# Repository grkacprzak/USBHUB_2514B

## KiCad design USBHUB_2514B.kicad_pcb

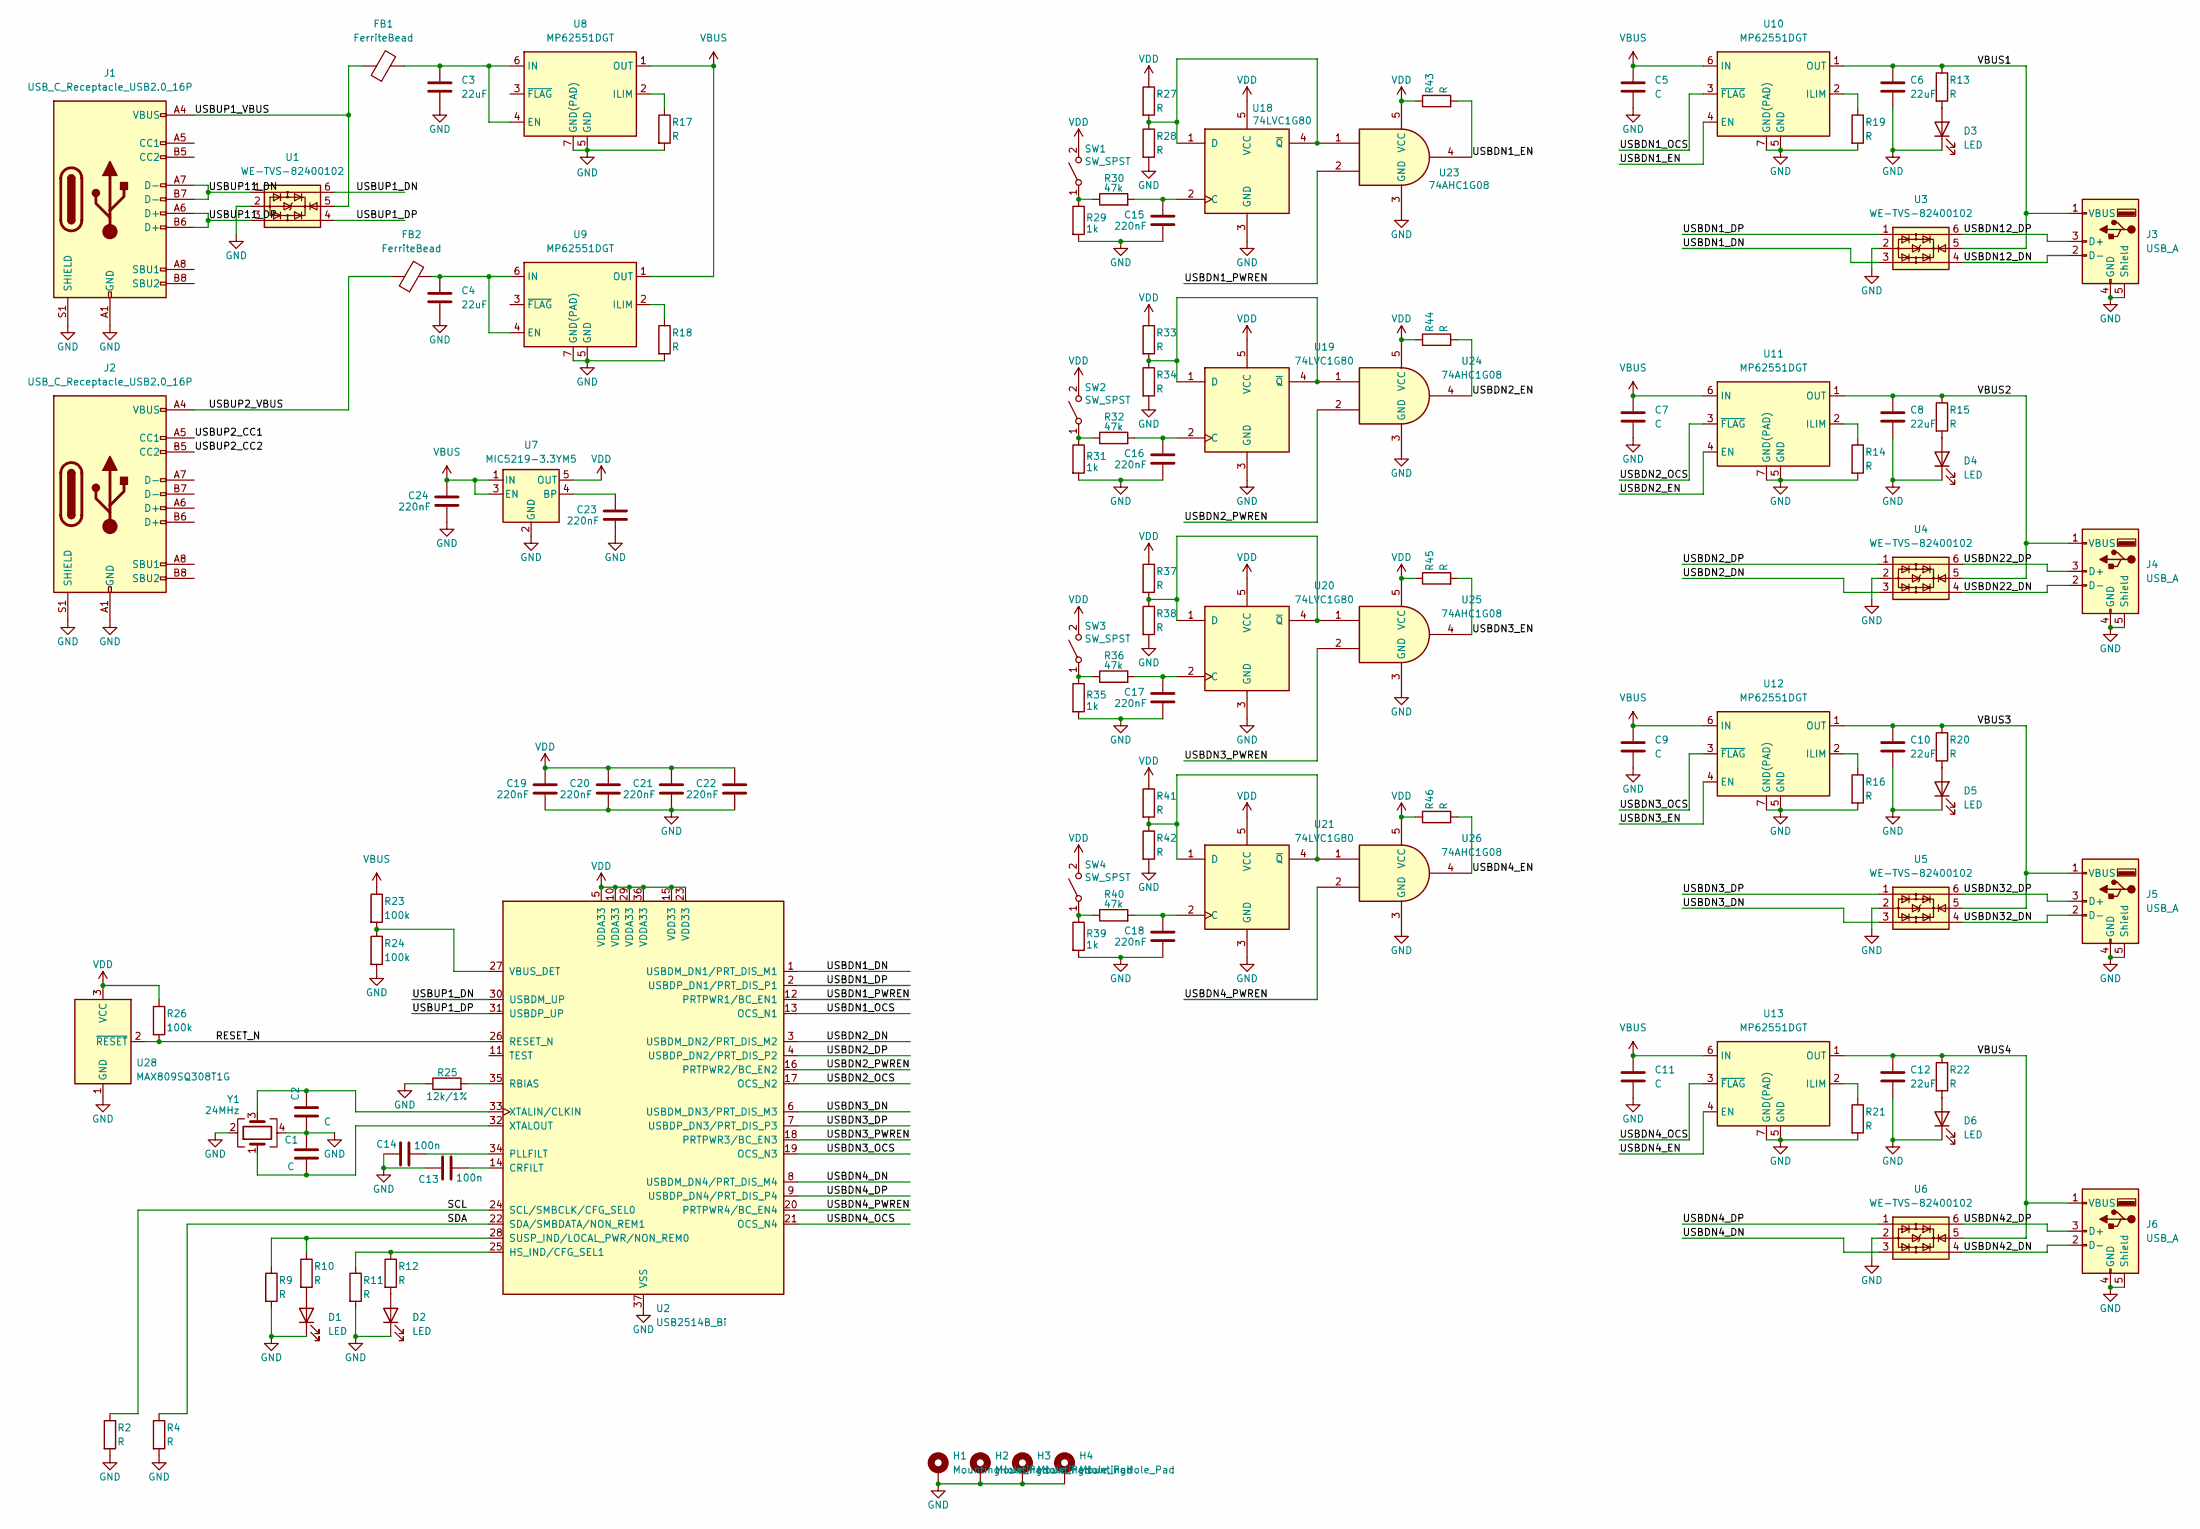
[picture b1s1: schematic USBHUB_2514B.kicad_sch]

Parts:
C1, C2, C5, C7, C9, C11: C; C_0402_1005Metric
C3, C4, C6, C8, C10, C12: 22uF; C_0805_2012Metric
C13, C14: 100n; C_0402_1005Metric
C15, C16, C17, C18, C19, C20, C21, C22, C23, C24: 220nF; C_0402_1005Metric
D1, D2, D3, D4, D5, D6: LED; LED_0603_1608Metric
FB1, FB2: FerriteBead; L_0805_2012Metric
H1, H2, H3, H4: MountingHole_Pad; MountingHole_2.5mm_Pad
J1, J2: USB_C_Receptacle_USB2.0_16P; USB_C_Receptacle_Wuerth_629722000214
J3, J4, J5, J6: USB_A; USB_A_Wuerth_614004185023_Vertical
R2, R4, R9, R10, R11, R12, R13, R14, R15, R16, R17, R18, R19, R20, R21, R22, R27, R28, R33, R34, R37, R38, R41, R42, R43, R44, R45, R46: R; R_0402_1005Metric
R23, R24, R26: 100k; R_0402_1005Metric
R25: 12k/1%; R_0402_1005Metric
R29, R31, R35, R39: 1k; R_0402_1005Metric
R30, R32, R36, R40: 47k; R_0402_1005Metric
SW1, SW2, SW3, SW4: SW_SPST; SW_PUSH_6mm_H9.5mm
U1, U3, U4, U5, U6: WE-TVS-82400102; SOT-363_SC-70-6
U2: USB2514B_Bi; QFN-36-1EP_6x6mm_P0.5mm_EP3.7x3.7mm
U7: MIC5219-3.3YM5; SOT-23-5
U8, U9, U10, U11, U12, U13: MP62551DGT; DFN-6-1EP_2x2mm_P0.65mm_EP1x1.6mm
U18, U19, U20, U21: 74LVC1G80; SOT-353_SC-70-5
U23, U24, U25, U26: 74AHC1G08; SOT-353_SC-70-5
U28: MAX809SQ308T1G; SOT-323_SC-70
Y1: 24MHz; Crystal_SMD_2520-4Pin_2.5x2.0mm

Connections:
/RESET_N: R26.2, U2.26 (RESET_N), U28.2 (~RESET)
/SCL: R2.1, U2.24 (SCL/SMBCLK/CFG_SEL0)
/SDA: R4.1, U2.22 (SDA/SMBDATA/NON_REM1)
/USBDN1_DN: U2.1 (USBDM_DN1/PRT_DIS_M1), U3.3
/USBDN1_DP: U2.2 (USBDP_DN1/PRT_DIS_P1), U3.1
/USBDN1_EN: R43.2, U10.4 (EN), U23.4
/USBDN1_OCS: U2.13 (OCS_N1), U10.3 (~FLAG)
/USBDN1_PWREN: U2.12 (PRTPWR1/BC_EN1), U23.2
/USBDN2_DN: U2.3 (USBDM_DN2/PRT_DIS_M2), U4.3
/USBDN2_DP: U2.4 (USBDP_DN2/PRT_DIS_P2), U4.1
/USBDN2_EN: R44.2, U11.4 (EN), U24.4
/USBDN2_OCS: U2.17 (OCS_N2), U11.3 (~FLAG)
/USBDN2_PWREN: U2.16 (PRTPWR2/BC_EN2), U24.2
/USBDN3_DN: U2.6 (USBDM_DN3/PRT_DIS_M3), U5.3
/USBDN3_DP: U2.7 (USBDP_DN3/PRT_DIS_P3), U5.1
/USBDN3_EN: R45.2, U12.4 (EN), U25.4
/USBDN3_OCS: U2.19 (OCS_N3), U12.3 (~FLAG)
/USBDN3_PWREN: U2.18 (PRTPWR3/BC_EN3), U25.2
/USBDN4_DN: U2.8 (USBDM_DN4/PRT_DIS_M4), U6.3
/USBDN4_DP: U2.9 (USBDP_DN4/PRT_DIS_P4), U6.1
/USBDN4_EN: R46.2, U13.4 (EN), U26.4
/USBDN4_OCS: U2.21 (OCS_N4), U13.3 (~FLAG)
/USBDN4_PWREN: U2.20 (PRTPWR4/BC_EN4), U26.2
/USBDN12_DN: J3.2 (D-), U3.4
/USBDN12_DP: J3.3 (D+), U3.6
/USBDN22_DN: J4.2 (D-), U4.4
/USBDN22_DP: J4.3 (D+), U4.6
/USBDN32_DN: J5.2 (D-), U5.4
/USBDN32_DP: J5.3 (D+), U5.6
/USBDN42_DN: J6.2 (D-), U6.4
/USBDN42_DP: J6.3 (D+), U6.6
/USBUP1_DN: U1.6, U2.30 (USBDM_UP)
/USBUP1_DP: U1.4, U2.31 (USBDP_UP)
/USBUP1_VBUS: FB1.1, J1.A4 (VBUS), J1.A9 (VBUS), J1.B4 (VBUS), J1.B9 (VBUS), U1.5
/USBUP2_CC1: J2.A5 (CC1)
/USBUP2_CC2: J2.B5 (CC2)
/USBUP2_VBUS: FB2.1, J2.A4 (VBUS), J2.A9 (VBUS), J2.B4 (VBUS), J2.B9 (VBUS)
/USBUP11_DN: J1.A7 (D-), J1.B7 (D-), U1.1
/USBUP11_DP: J1.A6 (D+), J1.B6 (D+), U1.3
/VBUS1: C6.1, J3.1 (VBUS), R13.1, U3.5, U10.1 (OUT)
/VBUS2: C8.1, J4.1 (VBUS), R15.1, U4.5, U11.1 (OUT)
/VBUS3: C10.1, J5.1 (VBUS), R20.1, U5.5, U12.1 (OUT)
/VBUS4: C12.1, J6.1 (VBUS), R22.1, U6.5, U13.1 (OUT)
GND: C1.1, C2.1, C3.2, C4.2, C5.2, C6.2, C7.2, C8.2, C9.2, C10.2, C11.2, C12.2, C13.2, C14.2, C15.2, C16.2, C17.2, C18.2, C19.2, C20.2, C21.2, C22.2, C23.2, C24.2, D1.1 (K), D2.1 (K), D3.1 (K), D4.1 (K), D5.1 (K), D6.1 (K), H1.1, H2.1, H3.1, H4.1, J1.A1 (GND), J1.A12 (GND), J1.B1 (GND), J1.B12 (GND), J1.S1 (SHIELD), J2.A1 (GND), J2.A12 (GND), J2.B1 (GND), J2.B12 (GND), J2.S1 (SHIELD), J3.4 (GND), J3.5 (Shield), J4.4 (GND), J4.5 (Shield), J5.4 (GND), J5.5 (Shield), J6.4 (GND), J6.5 (Shield), R2.2, R4.2, R9.2, R11.2, R14.2, R16.2, R17.2, R18.2, R19.2, R21.2, R24.2, R25.1, R28.2, R29.2, R31.2, R34.2, R35.2, R38.2, R39.2, R42.2, U1.2, U2.37 (VSS), U3.2, U4.2, U5.2, U6.2, U7.2 (GND), U8.5 (GND), U8.7 (GND(PAD)), U9.5 (GND), U9.7 (GND(PAD)), U10.5 (GND), U10.7 (GND(PAD)), U11.5 (GND), U11.7 (GND(PAD)), U12.5 (GND), U12.7 (GND(PAD)), U13.5 (GND), U13.7 (GND(PAD)), U18.3 (GND), U19.3 (GND), U20.3 (GND), U21.3 (GND), U23.3 (GND), U24.3 (GND), U25.3 (GND), U26.3 (GND), U28.1 (GND), Y1.2, Y1.4
unnamed: D1.2 (A), R10.2
unnamed: D2.2 (A), R12.2
unnamed: D3.2 (A), R13.2
unnamed: D4.2 (A), R15.2
unnamed: D5.2 (A), R20.2
unnamed: D6.2 (A), R22.2
unnamed: R29.1, R30.1, SW1.1 (A)
unnamed: R31.1, R32.1, SW2.1 (A)
unnamed: R35.1, R36.1, SW3.1 (A)
unnamed: R39.1, R40.1, SW4.1 (A)
unnamed: C13.1, U2.14 (CRFILT)
unnamed: R11.1, R12.1, U2.25 (HS_IND/CFG_SEL1)
unnamed: C14.1, U2.34 (PLLFILT)
unnamed: R25.2, U2.35 (RBIAS)
unnamed: R9.1, R10.1, U2.28 (SUSP_IND/LOCAL_PWR/NON_REM0)
unnamed: R23.2, R24.1, U2.27 (VBUS_DET)
unnamed: C2.2, U2.33 (XTALIN/CLKIN), Y1.3
unnamed: C1.2, U2.32 (XTALOUT), Y1.1
unnamed: C23.1, U7.4 (BP)
unnamed: C3.1, FB1.2, U8.4 (EN), U8.6 (IN)
unnamed: R17.1, U8.2 (ILIM)
unnamed: C4.1, FB2.2, U9.4 (EN), U9.6 (IN)
unnamed: R18.1, U9.2 (ILIM)
unnamed: R19.1, U10.2 (ILIM)
unnamed: R14.1, U11.2 (ILIM)
unnamed: R16.1, U12.2 (ILIM)
unnamed: R21.1, U13.2 (ILIM)
unnamed: C15.1, R30.2, U18.2 (C)
unnamed: R27.2, R28.1, U18.1 (D), U18.4 (~Q), U23.1
unnamed: C16.1, R32.2, U19.2 (C)
unnamed: R33.2, R34.1, U19.1 (D), U19.4 (~Q), U24.1
unnamed: C17.1, R36.2, U20.2 (C)
unnamed: R37.2, R38.1, U20.1 (D), U20.4 (~Q), U25.1
unnamed: C18.1, R40.2, U21.2 (C)
unnamed: R41.2, R42.1, U21.1 (D), U21.4 (~Q), U26.1
VBUS: C5.1, C7.1, C9.1, C11.1, C24.1, R23.1, U7.1 (IN), U7.3 (EN), U8.1 (OUT), U9.1 (OUT), U10.6 (IN), U11.6 (IN), U12.6 (IN), U13.6 (IN)
VDD: C19.1, C20.1, C21.1, C22.1, R26.1, R27.1, R33.1, R37.1, R41.1, R43.1, R44.1, R45.1, R46.1, SW1.2 (B), SW2.2 (B), SW3.2 (B), SW4.2 (B), U2.5 (VDDA33), U2.10 (VDDA33), U2.15 (VDD33), U2.23 (VDD33), U2.29 (VDDA33), U2.36 (VDDA33), U7.5 (OUT), U18.5 (VCC), U19.5 (VCC), U20.5 (VCC), U21.5 (VCC), U23.5 (VCC), U24.5 (VCC), U25.5 (VCC), U26.5 (VCC), U28.3 (VCC)

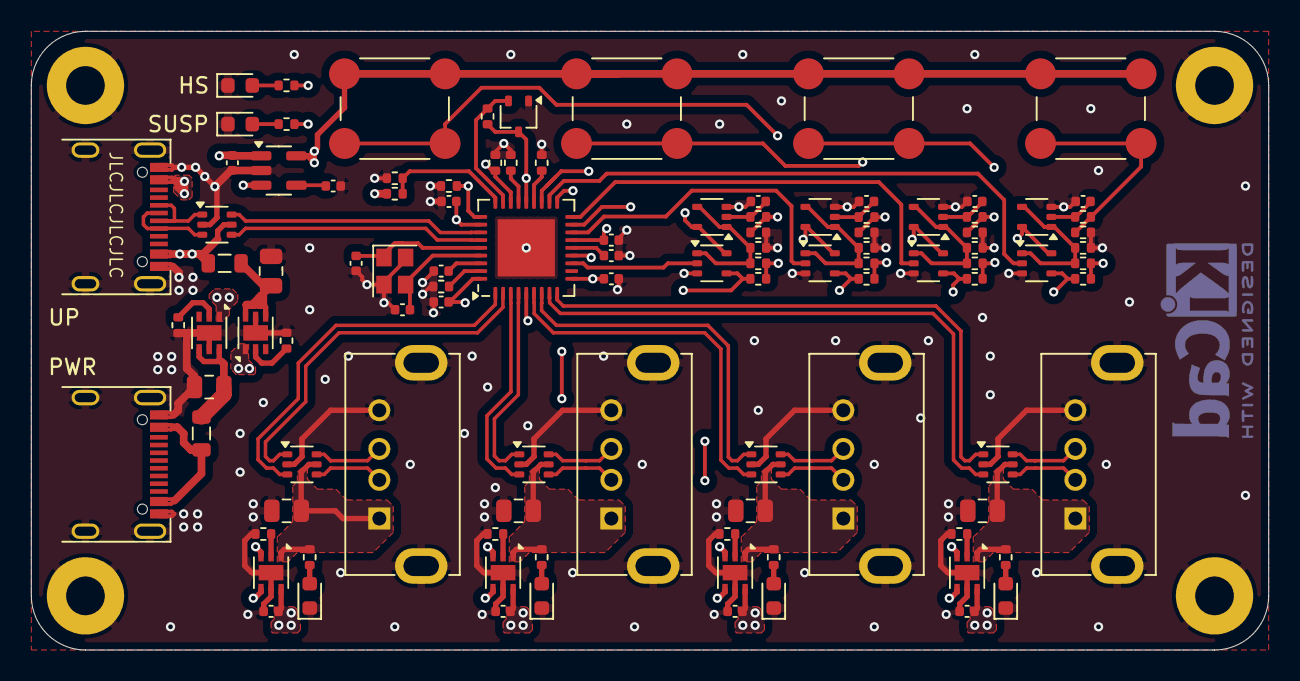
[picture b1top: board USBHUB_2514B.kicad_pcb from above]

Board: 4 copper layers, 80.0 x 40.0 mm, 109 parts (0 on the bottom side), 79 nets.

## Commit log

2024-10-07 prduction ver: a
2024-10-07 fix gitignore ~*
